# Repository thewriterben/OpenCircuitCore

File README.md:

# OpenCircuitCore

The electronics engine of the OpenDesignCore platform: circuits designed, verified, and manufactured through KiCad, scripted.

**Status:** pre-alpha. Toolchain decided and verified present (ADR-0003); no reference board yet.

## What it is

- **Substrate:** [KiCad](https://kicad.org) 10.x — schematic capture, ERC, PCB layout, DRC, footprint/symbol libraries, and fab outputs. Driven through `kicad-cli` and scripts, not by hand in the GUI.
- **BOM:** generated from the design, part references resolved against [OpenPartsCore](https://github.com/thewriterben/OpenPartsCore); pricing and stock fetched live from distributor APIs by consumers, never stored.
- **Co-design bridge:** `kicad-cli pcb export step|stl` emits board geometry that OpenDesignCore's mesh import boundary consumes — so an enclosure can be fitted to the actual board, not to a guess.
- **Boundary:** KiCad (GPLv3) is invoked strictly as an external tool — CLI/IPC, never linked (ADR-0002).

## Why not atopile

It was the original choice (ADR-0001) and was dropped the same day on evidence: the CLI is maintenance-only, 0.16+ moved to a hosted browser workspace, and the last CLI release will not install without a C++ toolchain. This platform is local-first and offline-capable everywhere else; the electronics half is not going to be the exception. Full reasoning in ADR-0003. tscircuit stays on the watch list.

## What it is not

- Not a parts database — that's OpenPartsCore.
- Not a fabricator — outputs hand off to local fabrication or the Project BINGO network.
- No invented component data: every part fact traces to OpenPartsCore (cited) or a datasheet.

## Planned shape (see ARCHITECTURE.md)

```
design scripts → KiCad project → ERC → DRC → gerbers + BOM + STEP/STL + provenance record
```

## License

Apache-2.0 — see [LICENSE](LICENSE).

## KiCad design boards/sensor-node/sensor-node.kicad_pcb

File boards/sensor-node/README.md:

# sensor-node

An ESP32-S3-WROOM-1 with a BME280 on I2C, a 4-pin sensor/power header and a 6-pin programming header. The first board here that is a **device**, and the first whose **firmware pin map is derived from the same netlist as the board** (OpenDesignCore `wiki/concepts/device-pipeline.md`, Phase 2).

## What is generated from what

```
scripts/make_sensor_node.py      PARTS (pin -> net)            -> sensor-node.kicad_sch
kicad-cli sch erc / export netlist                             -> erc-report.txt, sensor-node.net
scripts/make_sensor_node_board.py  PARTS + PLACEMENT + .net     -> sensor-node.kicad_pcb, board.manifest.json
scripts/route_board.py             .kicad_pcb (+ FreeRouting)   -> .dsn, .ses, routing.json, drc-report.txt
scripts/make_bom.py                opc_id fields + OpenPartsCore -> bom.csv, bom.json
scripts/make_firmware.py           .net + OpenPartsCore          -> firmware/{pins.rs, pins.h, firmware.manifest.json}
kicad-cli pcb export step|stl                                   -> sensor-node.step, .stl (enclosure co-design)
scripts/emit_provenance.py                                      -> sensor-node.provenance.json
```

Nothing downstream of the schematic restates connectivity. The board binds pads to the netlist's nets; the firmware reads GPIO numbers out of the netlist's module pin names (`IO8` on the SDA net, `IO9` on the SCL net) and the BME280 address out of where SDO is tied. Change a wire in `PARTS` and everything else follows or refuses.

## Regenerate

```
python scripts/make_sensor_node.py
cd boards/sensor-node
kicad-cli sch erc --exit-code-violations --severity-error -o erc-report.txt sensor-node.kicad_sch
kicad-cli sch export netlist -o sensor-node.net sensor-node.kicad_sch
cd ../..
python scripts/lf.py boards/sensor-node/erc-report.txt boards/sensor-node/sensor-node.net   # kicad-cli writes CRLF; provenance hashes LF
<KiCad>/bin/python.exe scripts/make_sensor_node_board.py
<KiCad>/bin/python.exe scripts/apply_fab_profile.py boards/sensor-node/sensor-node.kicad_pcb jlcpcb-2layer-1oz
kicad-cli pcb drc --severity-error -o boards/sensor-node/drc-report.txt boards/sensor-node/sensor-node.kicad_pcb
python scripts/lf.py boards/sensor-node/drc-report.txt
<KiCad>/bin/python.exe scripts/route_board.py boards/sensor-node/sensor-node.kicad_pcb --freerouting <freerouting-2.5.0.jar> --java <Java 25 java.exe>
<KiCad>/bin/python.exe scripts/add_ground_pour.py boards/sensor-node/sensor-node.kicad_pcb   # after routing, never before
kicad-cli pcb drc --severity-error -o boards/sensor-node/drc-report.txt boards/sensor-node/sensor-node.kicad_pcb
kicad-cli pcb export gerbers --layers "F.Cu,B.Cu,F.Mask,B.Mask,F.Paste,B.Paste,F.Silkscreen,B.Silkscreen,Edge.Cuts" -o boards/sensor-node/fab/ boards/sensor-node/sensor-node.kicad_pcb
kicad-cli pcb export drill --format excellon -o boards/sensor-node/fab/ boards/sensor-node/sensor-node.kicad_pcb
kicad-cli pcb export pos --format csv --units mm --side both --exclude-dnp -o boards/sensor-node/fab/sensor-node-pos.csv boards/sensor-node/sensor-node.kicad_pcb
python scripts/lf.py boards/sensor-node/drc-report.txt boards/sensor-node/fab/*
<KiCad>/bin/python.exe scripts/make_bom.py boards/sensor-node/sensor-node.kicad_pcb ../OpenPartsCore
python scripts/make_firmware.py boards/sensor-node/sensor-node.net --openpartscore ../OpenPartsCore --out boards/sensor-node/firmware
kicad-cli pcb export step --subst-models -o boards/sensor-node/sensor-node.step boards/sensor-node/sensor-node.kicad_pcb
kicad-cli pcb export stl -o boards/sensor-node/sensor-node.stl boards/sensor-node/sensor-node.kicad_pcb
python scripts/lf.py boards/sensor-node/sensor-node.step boards/sensor-node/sensor-node.stl   # ASCII exports, same rule
python scripts/emit_provenance.py boards/sensor-node && python scripts/verify_provenance.py boards/sensor-node
```

The board and routing scripts normalise their own outputs (`.net`, `.kicad_pcb`, `.dsn`) to LF; `lf.py` covers the kicad-cli reports and the ASCII STEP/STL exports.

## Current state (2026-11-04)

```
schematic: 13 parts, 44 pin connections, nets: +3V3, EN, GND, IO0, RXD0, SCL, SDA, TXD0
ERC:       Found 0 violations    (every unused module pin carries an explicit no-connect)
board:     outline 44.0 x 52.0 mm, 11 components, 4 x M3 holes; design rules = fab-profiles/jlcpcb-2layer-1oz
routing:   FreeRouting 2.5.0 (jar, Java 25): 143 tracks, 8 vias, routed_clean in routing.json
pour:      GND on F.Cu and B.Cu (1185 / 1482 mm^2 filled), stops at the antenna keepout y = 13.25 mm
DRC:       Found 0 DRC violations, Found 0 unconnected pads   (after pour, JLCPCB profile + sensor-node.kicad_dru)
warnings:  silk only: 70 silk_overlap, 63 silk_over_copper, 2 silk_edge_clearance (fab clips silk off pads)
fab/:      9 Gerber layers + job file, 1 Excellon drill (34 holes: 12 x 0.20, 8 x 0.30, 10 x 1.00, 4 x 3.20 NPTH), placement CSV
firmware:  I2C SDA=GPIO8 SCL=GPIO9, BME280 at 0x76 (SDO->GND, CSB->+3V3); strapping/USB pins clear
```

**Routed.** `route_board.py` exports DSN with `pcbnew.ExportSpecctraDSN`, runs FreeRouting (`-de … -do … -mp 20 --gui.enabled=false --router.automatic_neckdown=false`), imports the SES, re-runs DRC and writes `routing.json` with the hash of every input and output (router jar sha256 f6f51bb0…). Without `--freerouting` it exits 3 and keeps the DSN, and the board stays at 34 unconnected, which is the honest unrouted state. FreeRouting is GPL-3.0 and stays a separate process, like KiCad (DECISIONS.md). Regenerating the board with `make_sensor_node_board.py` produces an unrouted board again: re-apply the profile and re-route, in that order, because the DSN is exported from whatever the board holds (a routed board exported to DSN keeps its tracks).

**Two DRC hashes, both right.** `routing.json` records the DRC report as it stood straight after routing (`report_sha256` 72bd9a12…, board_sha256_after 4bed907b…). The GND pour and the proven DRC rule came after, in 9546499, and changed both the board and the report. The current report (b79007ac…) is the one `sensor-node.provenance.json` pins under `checks`. `routing.json` is a record of the routing step and is not rewritten; check the current board against the provenance file.

**Why the fab profile is applied before routing.** With KiCad's default 0.2 mm minimum, FreeRouting's fanout stage left 10–15 GND stubs at 0.15 mm where the module's 1.5 mm-pitch pads leave no room for 0.2 mm track plus 0.2 mm clearance; `--router.automatic_neckdown=false` reduced them (13 → 10 on this board) but did not remove them. JLCPCB's stated 2-layer minimum track is 0.10 mm (`fab-profiles/jlcpcb-2layer-1oz.json`, cited), so the board is checked against what the house will build, as `sensor-breakout` already is. Netclass widths stay 0.2 mm; only the minimums move.

**Use the `.jar`, not the native CLI.** `freerouting-cli-2.5.0-windows-x64.zip` (sha256 5750dc0b…) loads the DSN, then its routing thread dies on a GraalVM serialization error for `ComponentOutline` and the process hangs silently; `route_board.py` records `router_timeout`. Upstream freerouting/freerouting#957 confirms it and fixes it after 2.5.0. `freerouting-2.5.0.jar` needs Java 25 (class file 69; Java 21 fails with `UnsupportedClassVersionError`); pass the jar to `--freerouting` and the runtime to `--java` (default: `java` on PATH) and the script runs `java -jar`. Passing `-l en` makes it create an `en/freerouting.log` folder in the working directory; `route_board.py` does not pass it.

## Design notes, with sources

| item | choice | source |
|---|---|---|
| Module pins | pad numbers from KiCad `RF_Module:ESP32-S3-WROOM-1`; GND 1/40/41, 3V3 2, EN 3, IO0 27, RXD0 36, TXD0 37, IO8 12 (SDA), IO9 17 (SCL) | KiCad stock symbol; OpenPartsCore `electronic/esp32-s3-wroom-1` |
| Bus pins not strapping/USB | GPIO8/9 checked against `attributes.strapping_pins` {0, 3, 45, 46} and USB {19, 20} | OpenPartsCore entry, cited to the ESP32-S3-WROOM-1 datasheet "Strapping Pins" |
| BME280 I2C, address 0x76 | CSB → 3V3, SDO → GND | Bosch BME280 datasheet §6.2 |
| EN: 10k to 3V3 + 100n to GND; module supply 10u ∥ 100n | R3, C4; C2, C3 | Espressif ESP32-S3 Hardware Design Guidelines (power supply, chip enable). TODO(source): pin the section numbers |
| I2C pull-ups 4.7k | R1, R2 | design choice at 3.3 V |
| IO0 on PROG header, no pull-up | GPIO0 has the chip's internal weak pull-up; a programmer pulls it low | ESP32-S3 datasheet strapping description. TODO(source): confirm the module datasheet does not require an external resistor |
| Headers 2.54 mm 1x04 / 1x06 | J1 SENSOR (3V3, GND, SDA, SCL); J2 PROG (GND, TXD0, RXD0, IO0, EN, 3V3) | OpenPartsCore `electronic/pinheader-2.54-1x04`, `-1x06` (cited to the KiCad footprints; MPN-level data TODO) |
| Mounting holes below y = 17 mm | antenna keepout spans the board width above it | measured on `reference-esp32s3` |
| GND pour, both layers | clearance 0.30 mm, min width 0.25 mm, thermal reliefs 0.30 gap / 0.30 spoke, unconnected islands removed | design choice, wider than the profile's 0.10 mm so the pour never sets the tightest gap; `scripts/add_ground_pour.py`. The module footprint's own keepout rule area keeps copper out from under the antenna |
| `sensor-node.kicad_dru`: `npth_min_hole` 0.50 mm | JLCPCB "Min. Non-plated holes 0.50mm" | copied from `sensor-breakout`, **re-proven here**: at 5.0 mm it reports H1–H4 and nothing else (ADR-0006) |
| Design rules from `jlcpcb-2layer-1oz` | min track 0.10, clearance 0.10, through drill 0.15, via 0.25, hole-to-hole 0.45, copper-edge 0.20 mm | `fab-profiles/jlcpcb-2layer-1oz.json`, cited to JLCPCB's capabilities page; applied with `scripts/apply_fab_profile.py` (the board script's 0.2 mm drill relaxation for the module's thermal vias is superseded by the profile's 0.15) |

## Firmware hand-off

`firmware/pins.rs` is written for OBC-Prime's `Board { i2c: Option<(i32, i32)>, .. }`: `I2C = Some((8, 9))`, `BME280_I2C_ADDR = 0x76`. `firmware/pins.h` carries the same for an ESP-IDF build. `firmware.manifest.json` records the netlist sha256, both OpenPartsCore entry hashes, every derived value with the rule that produced it, and a **proposed** `espflash flash --monitor …` command with `executed: false`. The tool never flashes (ADR-0005; OpenDesignCore ADR-0009 execute-vs-propose). A netlist that puts SDA on a strapping pin is refused with the citation quoted (tested: exit 2, nothing written).

## Not done
- **An assembly order.** `fab/sensor-node-pos.csv` is KiCad's placement file (Ref, Val, Package, PosX, PosY, Rot, Side). JLCPCB's CPL wants Designator / Mid X / Mid Y / Layer / Rotation, and its rotation zero differs per package from KiCad's. Mapping columns is mechanical, but the rotation offsets have to be checked against JLCPCB's placement preview. They are not invented here. The BOM has no LCSC part numbers either, because OpenPartsCore entries are families, not MPNs.
- Silkscreen tidy-up: reference labels overlap at this placement density (warnings only).
- Stitching vias between the two GND pours; the router's GND tracks and vias carry the connection today.
- An OBC-Prime `Board` const for this node that `include!`s `pins.rs`; OBC-Prime targets pre-built dev boards today.
- Enclosure: done. OpenPartsCore `boards/opencircuitcore-sensor-node` (ADR-0008) records J1/J2 and their access from `sensor-node.step`, and OpenDesignCore `examples/sensor-node-enclosure` (0.1) is cut and printed from it. Open: the antenna keep-out around U1 is not yet pinned from Espressif's guidelines.

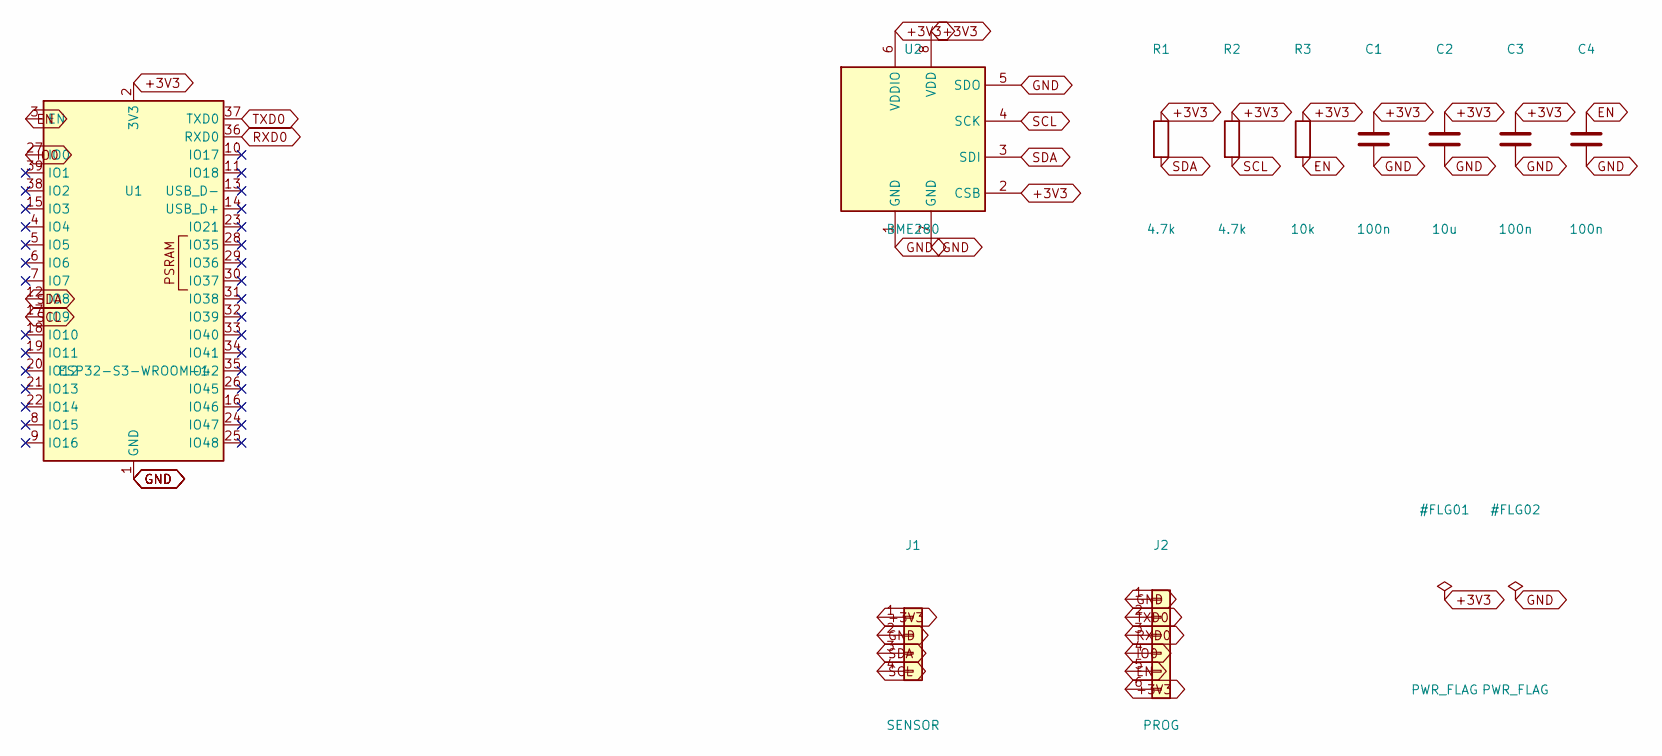
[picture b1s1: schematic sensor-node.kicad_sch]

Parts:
C1, C3, C4: 100n; C_0603_1608Metric
C2: 10u; C_0603_1608Metric
J1: SENSOR; PinHeader_1x04_P2.54mm_Vertical
J2: PROG; PinHeader_1x06_P2.54mm_Vertical
R1, R2: 4.7k; R_0603_1608Metric
R3: 10k; R_0603_1608Metric
U1: ESP32-S3-WROOM-1
U2: BME280; Bosch_LGA-8_2.5x2.5mm_P0.65mm_ClockwisePinNumbering

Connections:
+3V3: C1.1, C2.1, C3.1, J1.1, J2.6, R1.1, R2.1, R3.1, U1.2 (3V3), U2.2 (CSB), U2.6 (VDDIO), U2.8 (VDD)
EN: C4.1, J2.5, R3.2, U1.3 (EN)
GND: C1.2, C2.2, C3.2, C4.2, J1.2, J2.1, U1.1 (GND), U1.40 (GND), U1.41 (GND), U2.1 (GND), U2.5 (SDO), U2.7 (GND)
IO0: J2.4, U1.27 (IO0)
RXD0: J2.3, U1.36 (RXD0)
SCL: J1.4, R2.2, U1.17 (IO9), U2.4 (SCK)
SDA: J1.3, R1.2, U1.12 (IO8), U2.3 (SDI)
TXD0: J2.2, U1.37 (TXD0)

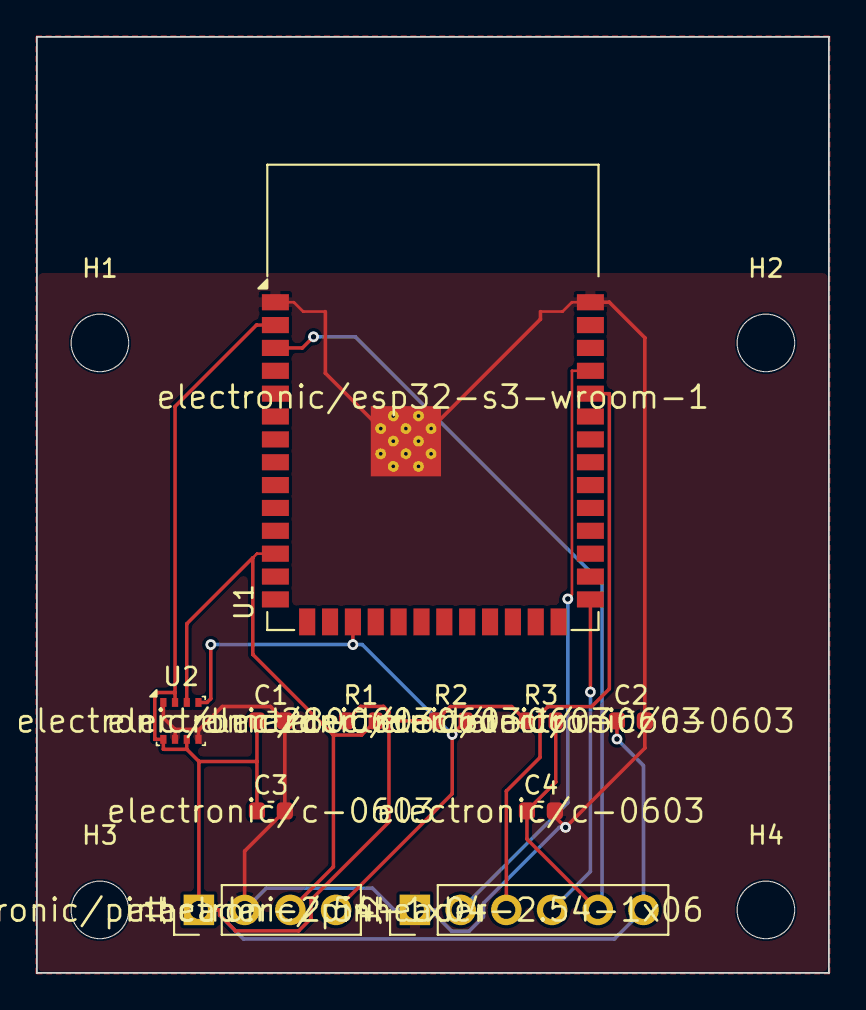
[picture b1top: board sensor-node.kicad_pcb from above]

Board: 2 copper layers, 44.0 x 52.0 mm, 15 parts (0 on the bottom side), 8 nets.

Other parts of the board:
H1, H2, H3, H4: MountingHole_3.2mm_M3

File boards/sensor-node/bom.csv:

refs,qty,value,footprint,opc_id,name,citation
U2,1,BME280,Bosch_LGA-8_2.5x2.5mm_P0.65mm_ClockwisePinNumbering,electronic/bme280,bme280,Oh-Ben-Claw registry/registry.json (generated from src/peripherals/registry.rs)
C1 C3 C4,3,100n,C_0603_1608Metric,electronic/c-0603,"Capacitor, 0603 (1608 metric)","IPC-SM-782A body size for 0603 (1608 metric), page 76, as cited by KiCad footprint Capacitor_SMD:C_0603_1608Metric. TODO(source): dielectric, tolerance and voltage ratings are vendor-specific and belong to a chosen MPN, not to the family. URL: the pcb-3d.com copy returned 404 on 2026-09-06; the url field now points at the Internet Archive snapshot of 2025-04-28 of the same file."
C2,1,10u,C_0603_1608Metric,electronic/c-0603,"Capacitor, 0603 (1608 metric)","IPC-SM-782A body size for 0603 (1608 metric), page 76, as cited by KiCad footprint Capacitor_SMD:C_0603_1608Metric. TODO(source): dielectric, tolerance and voltage ratings are vendor-specific and belong to a chosen MPN, not to the family. URL: the pcb-3d.com copy returned 404 on 2026-09-06; the url field now points at the Internet Archive snapshot of 2025-04-28 of the same file."
U1,1,ESP32-S3-WROOM-1,ESP32-S3-WROOM-1,electronic/esp32-s3-wroom-1,esp32-s3-wroom-1,"Espressif ESP32-S3-WROOM-1/1U Datasheet (identity and description). Migrated 2026-09-06 from OpenDesignCore data/parts/esp32-s3-wroom-1.json, where it had been entered 2026-08-15 from the same document."
J1,1,SENSOR,PinHeader_1x04_P2.54mm_Vertical,electronic/pinheader-2.54-1x04,"Pin header, 2.54 mm pitch, 1x04, through-hole vertical","KiCad footprint library Connector_PinHeader_2.54mm, footprint PinHeader_1x04_P2.54mm_Vertical, descr 'Through hole straight pin header, 1x04, 2.54mm pitch, single row' (generated by kicad-footprint-generator). TODO(source): current rating, plating and insulator height belong to a chosen MPN."
J2,1,PROG,PinHeader_1x06_P2.54mm_Vertical,electronic/pinheader-2.54-1x06,"Pin header, 2.54 mm pitch, 1x06, through-hole vertical","KiCad footprint library Connector_PinHeader_2.54mm, footprint PinHeader_1x06_P2.54mm_Vertical, descr 'Through hole straight pin header, 1x06, 2.54mm pitch, single row' (generated by kicad-footprint-generator). TODO(source): current rating, plating and insulator height belong to a chosen MPN."
R3,1,10k,R_0603_1608Metric,electronic/r-0603,"Resistor, 0603 (1608 metric)","IPC-SM-782A body size for 0603 (1608 metric), page 72, as cited by KiCad footprint Resistor_SMD:R_0603_1608Metric. TODO(source): tolerance, power and voltage ratings are vendor-specific and belong to a chosen MPN, not to the family. URL: the pcb-3d.com copy returned 404 on 2026-09-06; the url field now points at the Internet Archive snapshot of 2025-04-28 of the same file."
R1 R2,2,4.7k,R_0603_1608Metric,electronic/r-0603,"Resistor, 0603 (1608 metric)","IPC-SM-782A body size for 0603 (1608 metric), page 72, as cited by KiCad footprint Resistor_SMD:R_0603_1608Metric. TODO(source): tolerance, power and voltage ratings are vendor-specific and belong to a chosen MPN, not to the family. URL: the pcb-3d.com copy returned 404 on 2026-09-06; the url field now points at the Internet Archive snapshot of 2025-04-28 of the same file."

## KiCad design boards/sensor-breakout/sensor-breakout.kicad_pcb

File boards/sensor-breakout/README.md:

# sensor-breakout

A BME280 I2C breakout, and the first board here whose **connectivity comes from its schematic** rather than being asserted alongside it.

## Why it exists

`reference-esp32s3` proved the toolchain, but its schematic and board were generated independently — nothing tied them together, so nothing stopped them disagreeing. This board is generated from `make_reference_schematic.PARTS` (the same single source of truth as the schematic) and its pads are bound to nets read out of **the schematic's exported netlist**.

## Regenerate

```
# 1. schematic
python scripts/make_reference_schematic.py
kicad-cli sch erc --exit-code-violations --severity-error -o erc-report.txt sensor-subcircuit.kicad_sch
kicad-cli sch export netlist -o sensor-subcircuit.net sensor-subcircuit.kicad_sch

# 2. board, from that netlist
<KiCad>/bin/python.exe scripts/make_sensor_breakout.py
kicad-cli pcb drc --severity-error -o drc-report.txt sensor-breakout.kicad_pcb
```

## Current state

```
outline 22.0 x 26.0 mm, 4 component(s), 2 mounting hole(s)
nets from schematic: +3V3, GND, SCL, SDA

Found 0 violations
Found 10 unconnected items
```

**0 violations, 10 unconnected** is the correct and intended result. The board has real nets and an unrouted ratsnest — the state a router or a human takes over from. Verified from the saved file:

```
U2 [('1','GND'), ('2','+3V3'), ('3','SDA'), ('4','SCL'),
    ('5','GND'), ('6','+3V3'), ('7','GND'), ('8','+3V3')]
R1 [('1','+3V3'), ('2','SDA')]
```

That matches the schematic: CSB high for I2C, SDO low for address 0x76, R1 pulling SDA up to +3V3.

## Not done

- **Not routed.** No tracks, no copper pours. KiCad ships no autorouter and writing one is not this project's business; routing is interactive work, or an external router's.
- **No connector.** Power and I2C arrive at pads with no header footprint yet.
- Placement is hand-chosen in `PLACEMENT`, not optimised.

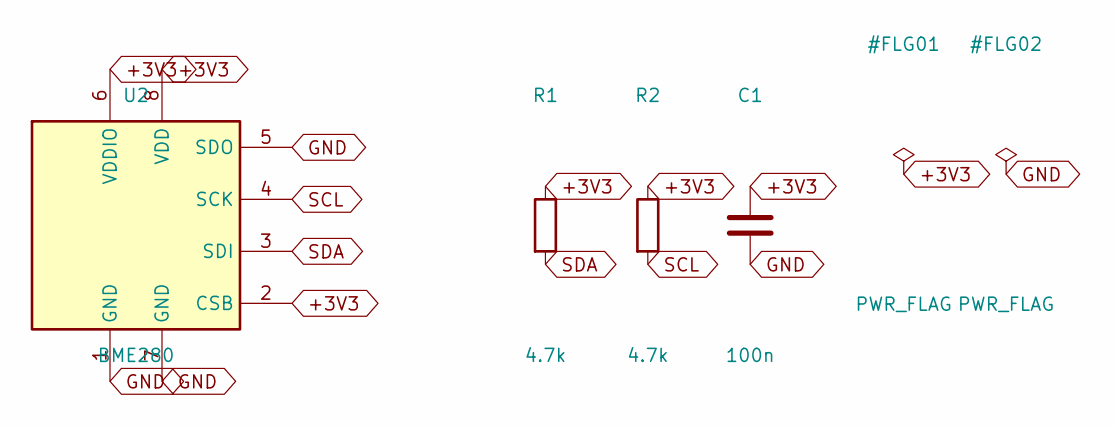
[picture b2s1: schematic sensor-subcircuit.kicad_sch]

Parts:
C1: 100n; C_0603_1608Metric
R1, R2: 4.7k; R_0603_1608Metric
U2: BME280; Bosch_LGA-8_2.5x2.5mm_P0.65mm_ClockwisePinNumbering

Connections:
+3V3: C1.1, R1.1, R2.1, U2.2 (CSB), U2.6 (VDDIO), U2.8 (VDD)
GND: C1.2, U2.1 (GND), U2.5 (SDO), U2.7 (GND)
SCL: R2.2, U2.4 (SCK)
SDA: R1.2, U2.3 (SDI)

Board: 2 copper layers, 6 parts (0 on the bottom side), 4 nets, no tracks yet.

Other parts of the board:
H1, H2: MountingHole_2.2mm_M2

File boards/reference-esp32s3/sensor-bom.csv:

"Reference","Value","Footprint","opc_id"
"C1","100n","Capacitor_SMD:C_0603_1608Metric","electronic/c-0603"
"R1,R2","4.7k","Resistor_SMD:R_0603_1608Metric","electronic/r-0603"
"U2","BME280","Package_LGA:Bosch_LGA-8_2.5x2.5mm_P0.65mm_ClockwisePinNumbering","electronic/bme280"
